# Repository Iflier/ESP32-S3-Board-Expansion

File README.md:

# ESP32-S3-Board-Expansion
ESP32-S3 Board Expansion

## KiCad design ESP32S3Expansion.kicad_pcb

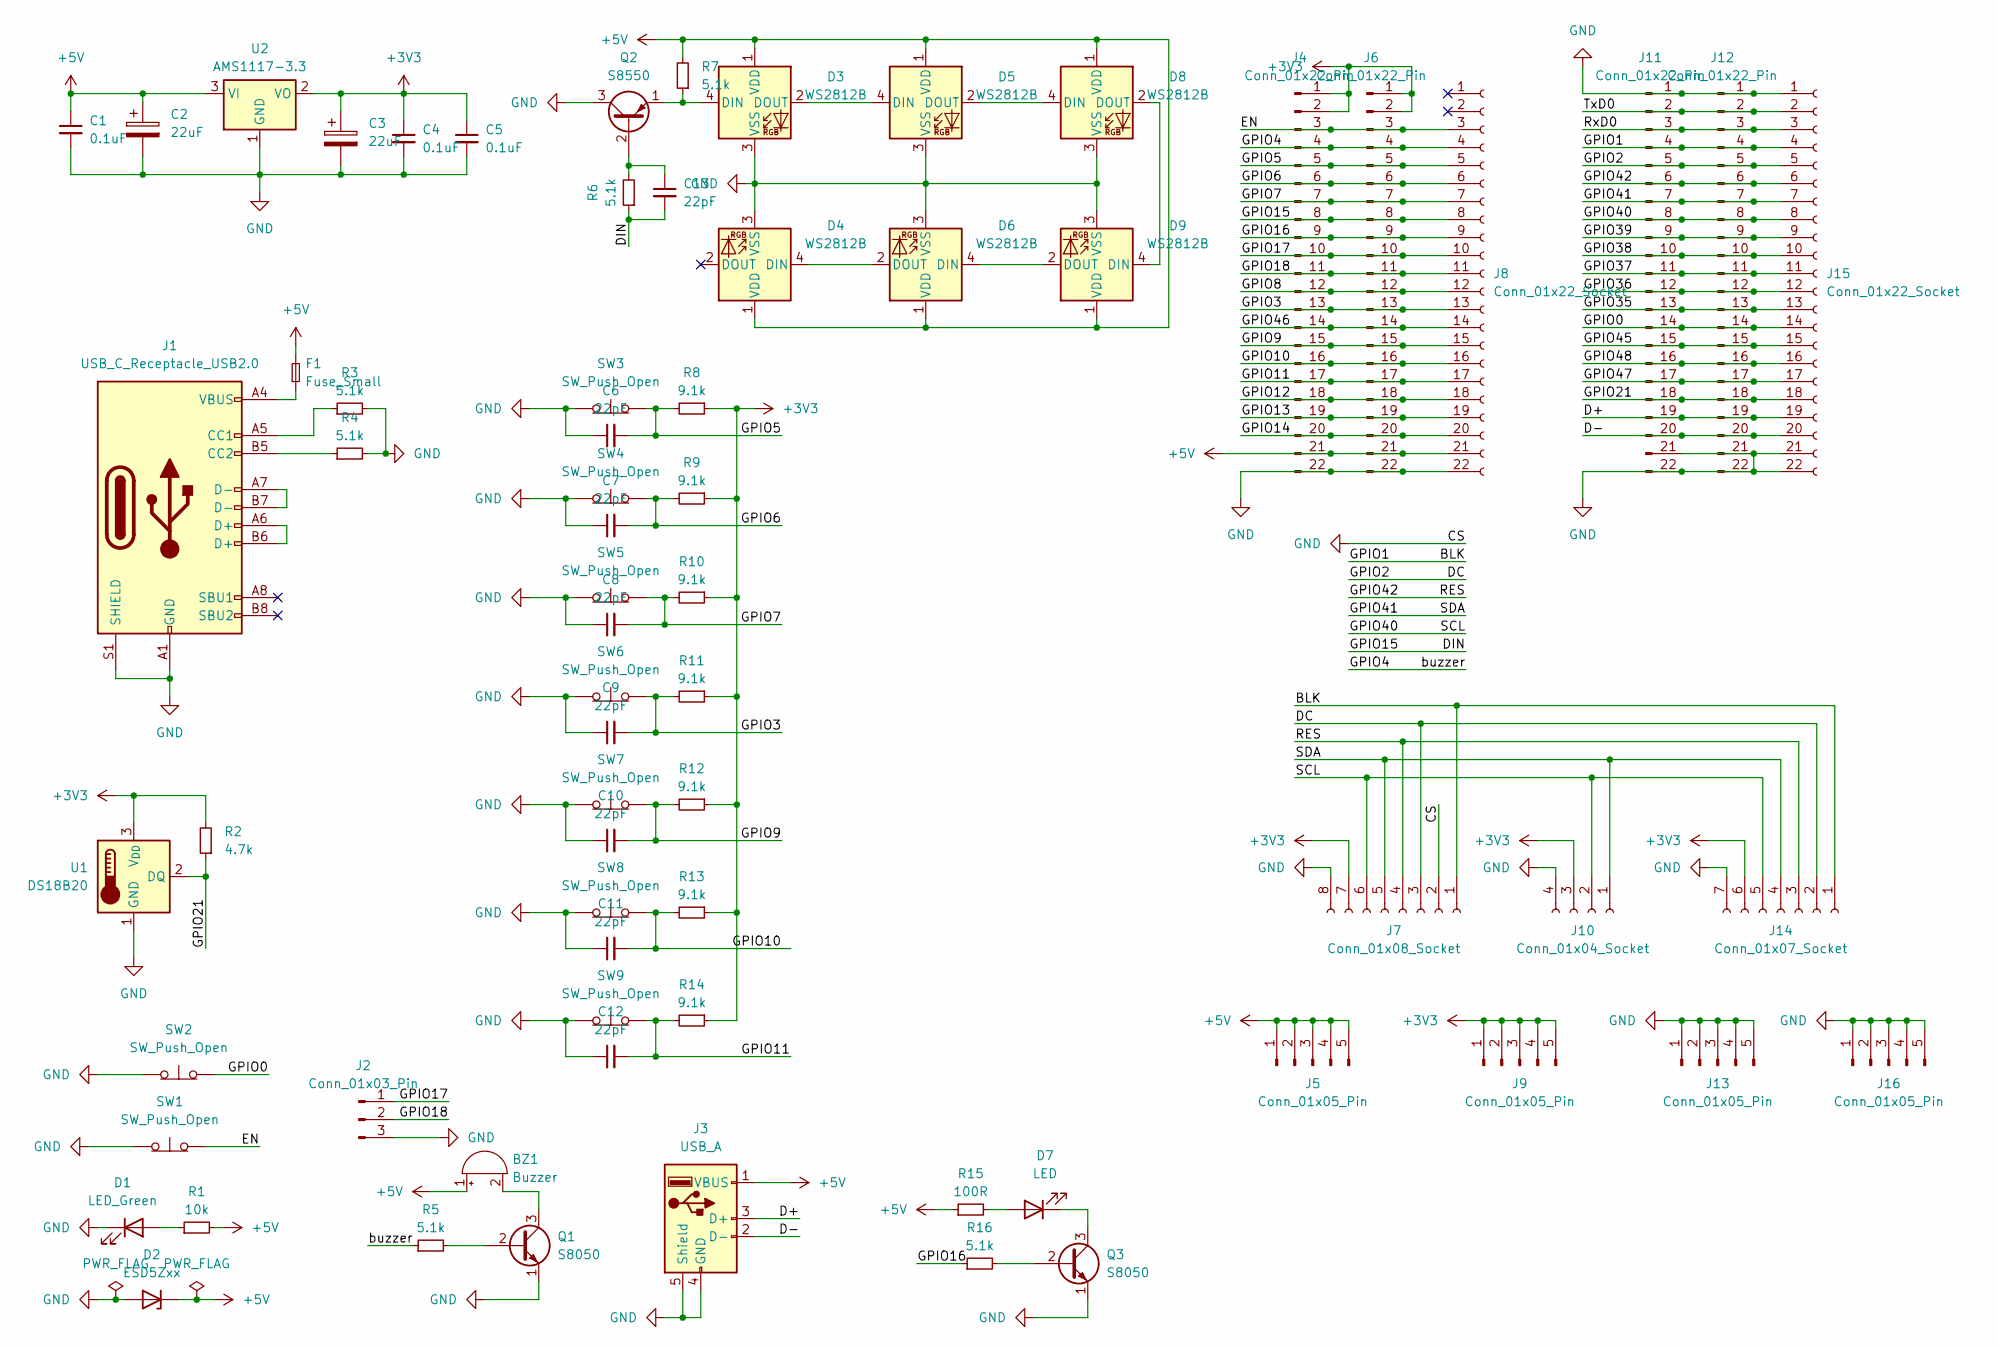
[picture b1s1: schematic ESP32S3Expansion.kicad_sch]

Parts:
BZ1: Buzzer; Buzzer_12x9.5RM7.6
C1, C4, C5: 0.1uF; C_1206_3216Metric_Pad1.33x1.80mm_HandSolder
C2, C3: 22uF; CP_Elec_4x5.4
C6, C7, C8, C9, C10, C11, C12, C13: 22pF; C_0805_2012Metric_Pad1.18x1.45mm_HandSolder
D1: LED_Green; LED_0805_2012Metric_Pad1.15x1.40mm_HandSolder
D2: ESD5Zxx; D_SMA_Handsoldering
D3, D4, D5, D6, D8, D9: WS2812B; LED_WS2812B_PLCC4_5.0x5.0mm_P3.2mm
D7: LED; LED_1206_3216Metric_Pad1.42x1.75mm_HandSolder
F1: Fuse_Small; Fuse_0805_2012Metric_Pad1.15x1.40mm_HandSolder
J1: USB_C_Receptacle_USB2.0; USB_C_Receptacle_Palconn_UTC16-G
J2: Conn_01x03_Pin; PinHeader_1x03_P2.54mm_Vertical
J3: USB_A; USB_A_Stewart_SS-52100-001_Horizontal
J4, J6, J11, J12: Conn_01x22_Pin; PinHeader_1x22_P2.54mm_Vertical
J5, J9, J13, J16: Conn_01x05_Pin; PinHeader_1x05_P2.54mm_Vertical
J7: Conn_01x08_Socket; PinSocket_1x08_P2.54mm_Vertical
J8, J15: Conn_01x22_Socket; PinSocket_1x22_P2.54mm_Vertical
J10: Conn_01x04_Socket; PinSocket_1x04_P2.54mm_Vertical
J14: Conn_01x07_Socket; PinSocket_1x07_P2.54mm_Vertical
Q1, Q3: S8050; SOT-23-3_S8050
Q2: S8550; SOT-23-3_S8050
R1: 10k; R_0805_2012Metric_Pad1.20x1.40mm_HandSolder
R2: 4.7k; R_0805_2012Metric_Pad1.20x1.40mm_HandSolder
R3, R4, R6, R7, R16: 5.1k; R_0805_2012Metric_Pad1.20x1.40mm_HandSolder
R5: 5.1k; R_1206_3216Metric_Pad1.30x1.75mm_HandSolder
R8, R9, R10, R11, R12, R13, R14: 9.1k; R_0805_2012Metric_Pad1.20x1.40mm_HandSolder
R15: 100R; R_0805_2012Metric_Pad1.20x1.40mm_HandSolder
SW1, SW2, SW3, SW4, SW5, SW6, SW7, SW8, SW9: SW_Push_Open; SW_SPST_CK_RS282G05A3
U1: DS18B20; TO-92_Inline_Wide
U2: AMS1117-3.3; SOT-223-3_TabPin2

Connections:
+3V3: C3.1, C4.1, C5.1, J4.1, J4.2, J6.1, J6.2, J7.7, J9.1, J9.2, J9.3, J9.4, J9.5, J10.3, J14.6, R2.2, R8.1, R9.1, R10.1, R11.1, R12.1, R13.1, R14.1, U1.3 (V_{DD}), U2.2 (VO)
+5V: BZ1.1 (-), C1.1, C2.1, D2.1 (K), D3.1 (VDD), D4.1 (VDD), D5.1 (VDD), D6.1 (VDD), D8.1 (VDD), D9.1 (VDD), F1.2, J3.1 (VBUS), J4.21, J5.1, J5.2, J5.3, J5.4, J5.5, J6.21, J8.21, R1.2, R7.2, R15.1, U2.3 (VI)
/BLK: J7.1, J11.4, J12.4, J14.1, J15.4
/D+: J3.3 (D+), J11.19, J12.19, J15.19
/D-: J3.2 (D-), J11.20, J12.20, J15.20
/DC: J7.3, J11.5, J12.5, J14.2, J15.5
/DIN: C13.2, J4.8, J6.8, J8.8, R6.1
/EN: J4.3, J6.3, J8.3, SW1.2 (B)
/GPIO0: J11.14, J12.14, J15.14, SW2.2 (B)
/GPIO3: C9.2, J4.13, J6.13, J8.13, R11.2, SW6.2 (B)
/GPIO4: J4.4, J6.4, J8.4, R5.1
/GPIO5: C6.2, J4.5, J6.5, J8.5, R8.2, SW3.2 (B)
/GPIO6: C7.2, J4.6, J6.6, J8.6, R9.2, SW4.2 (B)
/GPIO7: C8.2, J4.7, J6.7, J8.7, R10.2, SW5.2 (B)
/GPIO8: J4.12, J6.12, J8.12
/GPIO9: C10.2, J4.15, J6.15, J8.15, R12.2, SW7.2 (B)
/GPIO10: C11.2, J4.16, J6.16, J8.16, R13.2, SW8.2 (B)
/GPIO11: C12.2, J4.17, J6.17, J8.17, R14.2, SW9.2 (B)
/GPIO12: J4.18, J6.18, J8.18
/GPIO13: J4.19, J6.19, J8.19
/GPIO14: J4.20, J6.20, J8.20
/GPIO16: J4.9, J6.9, J8.9, R16.1
/GPIO17: J2.1, J4.10, J6.10, J8.10
/GPIO18: J2.2, J4.11, J6.11, J8.11
/GPIO21: J11.18, J12.18, J15.18, R2.1, U1.2 (DQ)
/GPIO35: J11.13, J12.13, J15.13
/GPIO36: J11.12, J12.12, J15.12
/GPIO37: J11.11, J12.11, J15.11
/GPIO38: J11.10, J12.10, J15.10
/GPIO39: J11.9, J12.9, J15.9
/GPIO40: J7.6, J10.2, J11.8, J12.8, J14.5, J15.8
/GPIO41: J7.5, J10.1, J11.7, J12.7, J14.4, J15.7
/GPIO42: J7.4, J11.6, J12.6, J14.3, J15.6
/GPIO45: J11.15, J12.15, J15.15
/GPIO46: J4.14, J6.14, J8.14
/GPIO47: J11.17, J12.17, J15.17
/GPIO48: J11.16, J12.16, J15.16
/RxD0: J11.3, J12.3, J15.3
/TxD0: J11.2, J12.2, J15.2
GND: C1.2, C2.2, C3.2, C4.2, C5.2, C6.1, C7.1, C8.1, C9.1, C10.1, C11.1, C12.1, D1.1 (K), D2.2 (A), D3.3 (VSS), D4.3 (VSS), D5.3 (VSS), D6.3 (VSS), D8.3 (VSS), D9.3 (VSS), J1.A1 (GND), J1.A12 (GND), J1.B1 (GND), J1.B12 (GND), J1.S1 (SHIELD), J2.3, J3.4 (GND), J3.5 (Shield), J4.22, J6.22, J7.2, J7.8, J8.22, J10.4, J11.1, J11.21, J11.22, J12.1, J12.21, J12.22, J13.1, J13.2, J13.3, J13.4, J13.5, J14.7, J15.1, J15.21, J15.22, J16.1, J16.2, J16.3, J16.4, J16.5, Q1.1 (E), Q2.3 (C), Q3.1 (E), R3.2, R4.2, SW1.1 (A), SW2.1 (A), SW3.1 (A), SW4.1 (A), SW5.1 (A), SW6.1 (A), SW7.1 (A), SW8.1 (A), SW9.1 (A), U1.1 (GND), U2.1 (GND)
unnamed: BZ1.2 (+), Q1.3 (C)
unnamed: D1.2 (A), R1.1
unnamed: D3.4 (DIN), Q2.1 (E), R7.1
unnamed: D3.2 (DOUT), D5.4 (DIN)
unnamed: D4.4 (DIN), D6.2 (DOUT)
unnamed: D5.2 (DOUT), D8.4 (DIN)
unnamed: D6.4 (DIN), D9.2 (DOUT)
unnamed: D7.2 (A), R15.2
unnamed: D7.1 (K), Q3.3 (C)
unnamed: D8.2 (DOUT), D9.4 (DIN)
unnamed: F1.1, J1.A4 (VBUS), J1.A9 (VBUS), J1.B4 (VBUS), J1.B9 (VBUS)
unnamed: J1.A5 (CC1), R3.1
unnamed: J1.B5 (CC2), R4.1
unnamed: J1.A6 (D+), J1.B6 (D+)
unnamed: J1.A7 (D-), J1.B7 (D-)
unnamed: Q1.2 (B), R5.2
unnamed: C13.1, Q2.2 (B), R6.2
unnamed: Q3.2 (B), R16.2

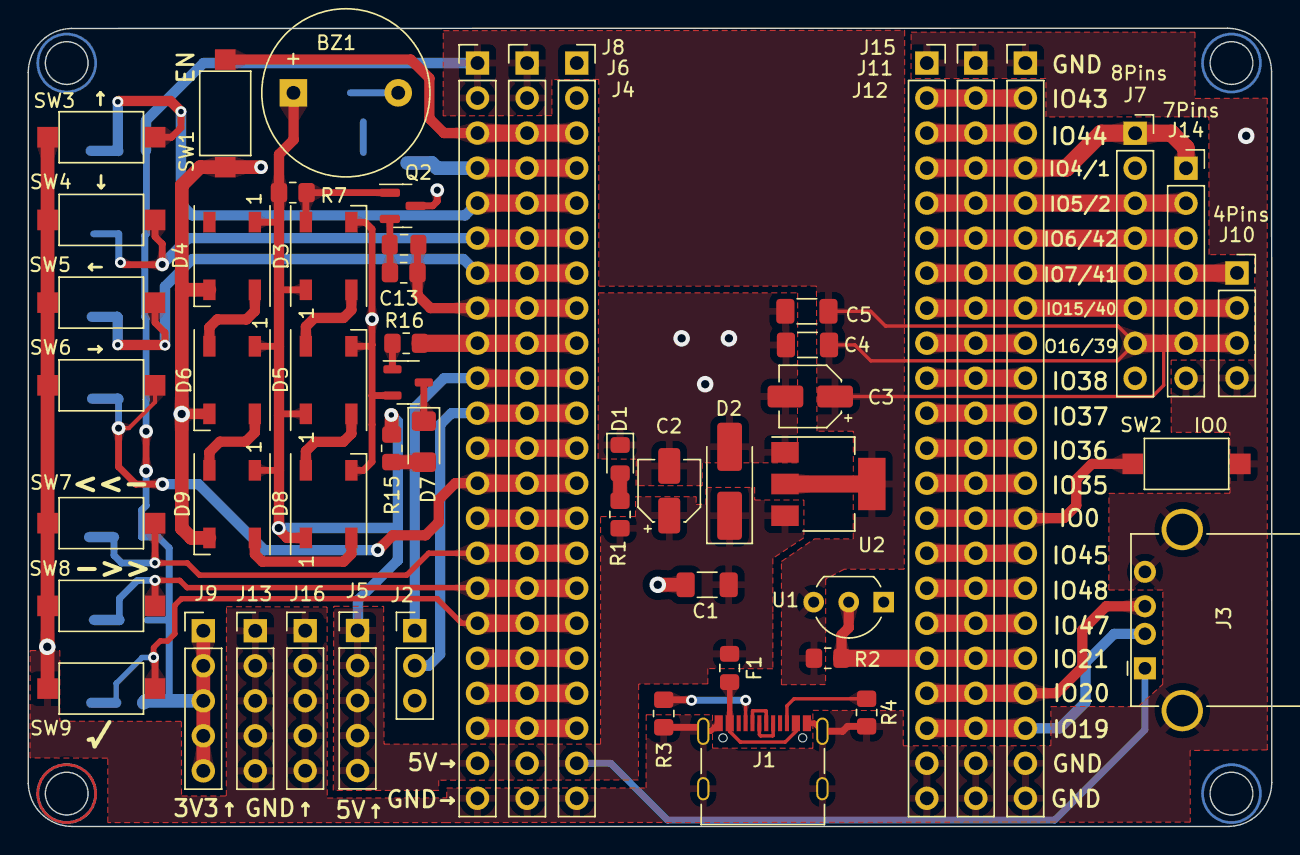
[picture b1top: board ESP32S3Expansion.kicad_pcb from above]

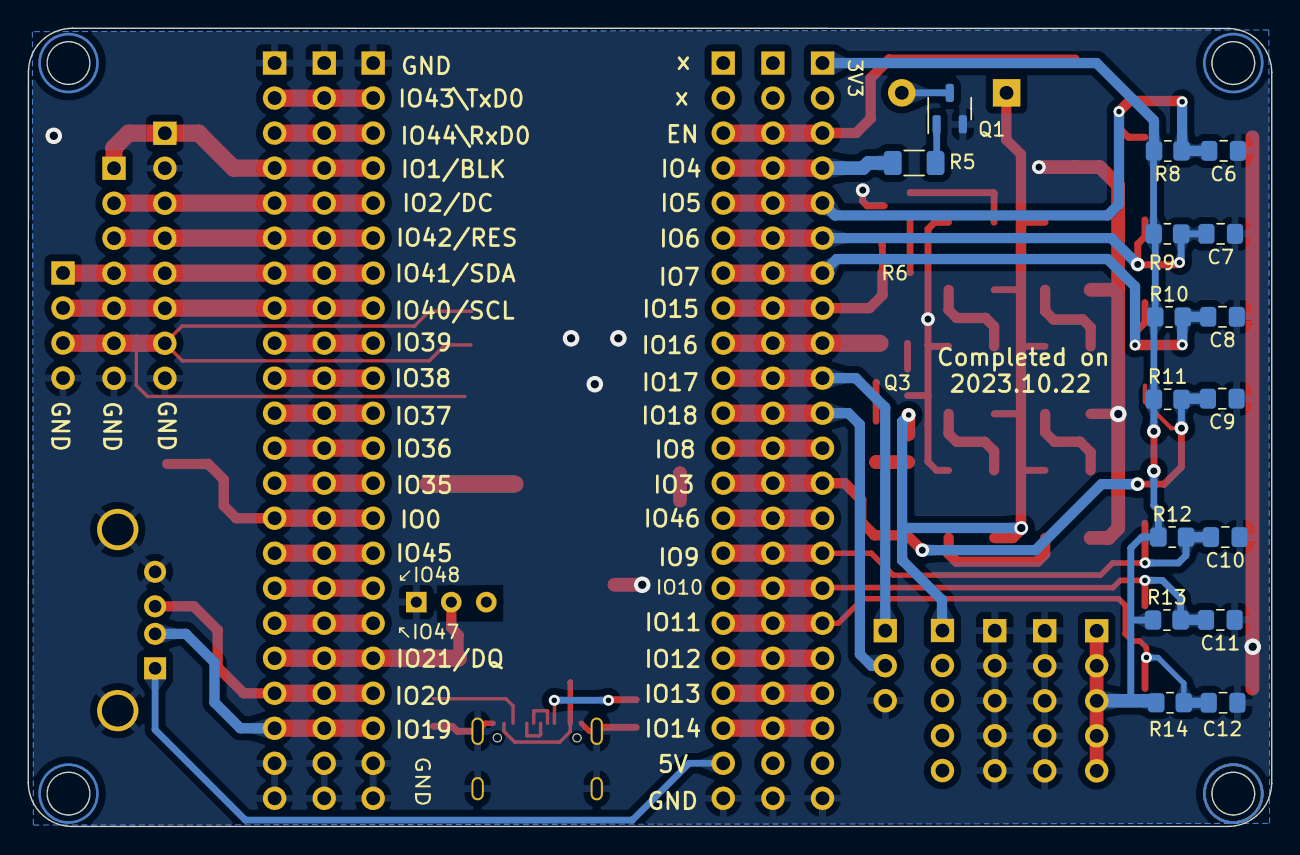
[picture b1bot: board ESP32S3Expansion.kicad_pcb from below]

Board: 2 copper layers, 90.2 x 57.9 mm, 70 parts (16 on the bottom side), 58 nets.

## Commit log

2023-12-02 upload project
    Upload Kicad Project files
